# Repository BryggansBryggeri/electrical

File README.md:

# electrical
Electronics, hardware schematics

## Ethernet Cable Wiring Guide
| Colour     	| Connector 	| Temp [DS18B20] 	| VFD  	| Pressure 	| Float switch 	| Albus 	|
|----------	|-------	|----------------	|------	|-------	|-------------	|-------	|
| Orange   	| 1     	| +              	| N/A  	| N/A   	| +           	| N/A   	|
| Blå      	| 2     	| -              	| N/A  	| N/A   	| -           	| N/A   	|
| Brun     	| 3     	| Data           	| N/A  	| N/A   	| N/A         	| N/A   	|
| Grön     	| 4     	| N/A            	| Dif+ 	| N/A   	| N/A         	| N/A   	|
| Grön/Vit 	| 5     	| N/A            	| Dif- 	| N/A   	| N/A         	| N/A   	|

## Panel mounted Contact Orientation

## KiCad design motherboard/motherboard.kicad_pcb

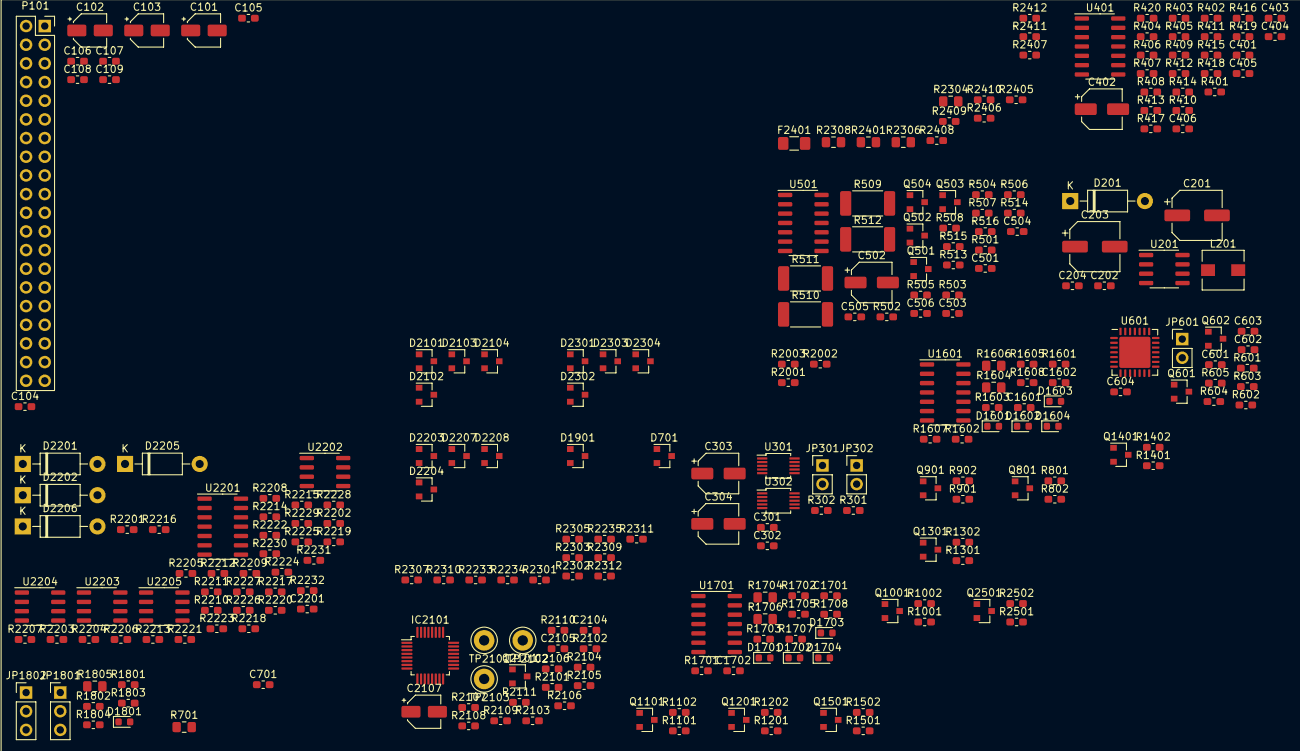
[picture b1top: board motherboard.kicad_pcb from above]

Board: 2 copper layers, 265 parts (0 on the bottom side), 179 nets, no tracks yet.

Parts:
C101, C102, C103, C2107: 1u; CP_Elec_4x5.4
C104, C105, C106, C202: 10n; C_0603_1608Metric_Pad1.05x0.95mm_HandSolder
C107, C108, C109: 100p; C_0603_1608Metric_Pad1.05x0.95mm_HandSolder
C201: 100u; CP_Elec_6.3x5.4_Nichicon
C203: 68u; CP_Elec_6.3x5.8
C204, C2106, C2201: 100n; C_0603_1608Metric_Pad1.05x0.95mm_HandSolder
C301, C302, C2105: 0.1u; C_0603_1608Metric_Pad1.05x0.95mm_HandSolder
C303, C304, C402, C502: 10u; CP_Elec_5x5.4
C401, C403, C404, C405, C406, C501, C503, C504, C505, C506: 2u2; C_0603_1608Metric_Pad1.05x0.95mm_HandSolder
C601, C602: 100pF; C_0603_1608Metric_Pad1.05x0.95mm_HandSolder
C603, C1601, C1701: 100nF; C_0603_1608Metric_Pad1.05x0.95mm_HandSolder
C604, C1602, C1702: 10pF; C_0603_1608Metric_Pad1.05x0.95mm_HandSolder
C701: 220n; C_0603_1608Metric_Pad1.05x0.95mm_HandSolder
C2104: 330n; C_0603_1608Metric_Pad1.05x0.95mm_HandSolder
D201: 1N5817; D_DO-41_SOD81_P10.16mm_Horizontal
D701, D1901, D2101, D2102, D2103, D2104, D2203, D2204, D2207, D2208, D2301, D2302, D2303, D2304: BAT54S; SOT-23
D1601, D1602, D1603, D1604, D1701, D1702, D1703, D1704, D1801: LED; LED_0603_1608Metric
D2201, D2202, D2205, D2206: 1N457; D_DO-41_SOD81_P10.16mm_Horizontal
F2401: 160mA; Fuse_1206_3216Metric_Pad1.42x1.75mm_HandSolder
IC2101: ADS124S08IPBSR; LQFP-32_5x5mm_P0.5mm
JP301, JP302, JP601: Jumper; PinHeader_1x02_P2.54mm_Vertical
JP1801, JP1802: Jumper_3_Bridged12; PinHeader_1x03_P2.54mm_Vertical
L201: 220n; L_Wuerth_HCI-5040
P101: Raspberry_Pi_+_Conn; PinSocket_2x20_P2.54mm_Vertical
Q501, Q502, Q503, Q504, Q601, Q602, Q801, Q901, Q1001, Q1101, Q1201, Q1301, Q1401, Q1501, Q2101, Q2501: Q_NMOS_GSD; SOT-23
R301, R302, R601, R602, R605, R2301, R2303, R2305, R2307: 10k; R_0603_1608Metric_Pad1.05x0.95mm_HandSolder
R401, R402, R403, R404, R501, R502, R503, R504: 22k; R_0603_1608Metric_Pad1.05x0.95mm_HandSolder
R405, R406, R407, R408, R505, R506, R507, R508: 1M; R_0603_1608Metric_Pad1.05x0.95mm_HandSolder
R409, R410, R411, R412: 3k9; R_0603_1608Metric_Pad1.05x0.95mm_HandSolder
R413, R414, R415, R416: 6k8; R_0603_1608Metric_Pad1.05x0.95mm_HandSolder
R417, R418, R419, R420: 1k2; R_0603_1608Metric_Pad1.05x0.95mm_HandSolder
R509, R510, R511, R512: 180R; R_2512_6332Metric_Pad1.52x3.35mm_HandSolder
R513, R514, R515, R516, R801, R901, R1001, R1101, R1201, R1301, R1401, R1501, R1801, R1802, R2107, R2211, R2212, R2227, R2228, R2501: 100k; R_0603_1608Metric_Pad1.05x0.95mm_HandSolder
R603, R604, R2110, R2213, R2214, R2215, R2216, R2229, R2230, R2231, R2232, R2309, R2310, R2311, R2312, R2405, R2406, R2407, R2408, R2409, R2410, R2411, R2412: 1k; R_0603_1608Metric_Pad1.05x0.95mm_HandSolder
R701, R1604, R1606, R1704, R1706, R1805: 220; R_0805_2012Metric_Pad1.15x1.40mm_HandSolder
R802, R902, R1002, R1102, R1202, R1302, R1402, R1502, R2502: 5.6; R_0603_1608Metric_Pad1.05x0.95mm_HandSolder
R1601, R1603, R1605, R1607, R1701, R1703, R1705, R1707: 4k7; R_0603_1608Metric_Pad1.05x0.95mm_HandSolder
R1602, R1608, R1702, R1708: 220; R_0603_1608Metric_Pad1.05x0.95mm_HandSolder
R1803: 3k3; R_0603_1608Metric_Pad1.05x0.95mm_HandSolder
R1804: 5k6; R_0603_1608Metric_Pad1.05x0.95mm_HandSolder
R2001, R2002: 100; R_0603_1608Metric_Pad1.05x0.95mm_HandSolder
R2003: 4.7k; R_0603_1608Metric_Pad1.05x0.95mm_HandSolder
R2101, R2103: R; R_0603_1608Metric_Pad1.05x0.95mm_HandSolder
R2102, R2104, R2105, R2106, R2108, R2109, R2111: 47R; R_0603_1608Metric_Pad1.05x0.95mm_HandSolder
R2201, R2202, R2217, R2218: 75R; R_0603_1608Metric_Pad1.05x0.95mm_HandSolder
R2203, R2204, R2219, R2220: 750R; R_0603_1608Metric_Pad1.05x0.95mm_HandSolder
R2205, R2207, R2208, R2210, R2221, R2223, R2224, R2226: 20k; R_0603_1608Metric_Pad1.05x0.95mm_HandSolder
R2206, R2209, R2222, R2225: 28k; R_0603_1608Metric_Pad1.05x0.95mm_HandSolder
R2233, R2234, R2235, R2302: 2k7; R_0603_1608Metric_Pad1.05x0.95mm_HandSolder
R2304, R2306, R2308, R2401: 120R; R_0805_2012Metric_Pad1.15x1.40mm_HandSolder
TP2101, TP2102, TP2103: TestPoint; TestPoint_Loop_D3.50mm_Drill1.4mm_Beaded
U201: LM2674M-12; SOIC-8_3.9x4.9mm_P1.27mm
U301, U302: MCP4728; MSOP-10_3x3mm_P0.5mm
U401, U501, U1601, U1701, U2201: LM324; SOIC-14_3.9x8.7mm_P1.27mm
U601: MCP23017_ML; QFN-28-1EP_6x6mm_P0.65mm_EP4.25x4.25mm
U2202, U2203, U2204, U2205: LM334M; SOIC-8_3.9x4.9mm_P1.27mm

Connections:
+3V3: C102.1, C105.1, C108.1, C2105.1, D1901.2, IC2101.15, IC2101.16, P101.1, Q601.1, Q602.1, Q2101.3, R601.2, R602.2, R2003.1
+5V: C101.1, C104.1, C107.1, C603.1, C604.1, C1601.1, C1602.1, C1701.1, C1702.1, C2104.1, C2106.1, C2201.1, IC2101.26, JP301.2, JP302.2, JP601.1, P101.2, P101.4, R603.1, R604.1, R701.1, U601.5, U1601.4, U1701.4, U2201.4
+12V: C203.1, C204.1, L201.2, U201.4, U401.4, U501.4
+24V: C103.1, C106.1, C109.1, C201.1, F2401.2, U201.5, U201.7
/ADC_START_SYNC: P101.36, R2102.2
/Analog inputs/10V_A: IC2101.3, R2309.1
/Analog inputs/10V_B: IC2101.2, R2310.1
/Analog inputs/10V_C: IC2101.32, R2311.1
/Analog inputs/10V_D: IC2101.31, R2312.1
/Analog inputs/20mA-1-4/A_in_low: R2401.1, R2405.2
/Analog inputs/20mA-1-4/B_in_low: R2304.1, R2406.2
/Analog inputs/20mA-1-4/C_in_low: R2306.1, R2407.2
/Analog inputs/20mA-1-4/D_in_low: R2308.1, R2408.2
/Analog inputs/20mA-1-4/Vref: D2301.2, D2302.2, D2303.2, D2304.2
/Analog inputs/20mA_A: IC2101.22, R2409.1
/Analog inputs/20mA_B: IC2101.21, R2410.1
/Analog inputs/20mA_C: IC2101.20, R2411.1
/Analog inputs/20mA_D: IC2101.19, R2412.1
/Analog inputs/PT100_A: IC2101.7, R2215.1
/Analog inputs/PT100_B: IC2101.6, R2231.1
/Analog inputs/PT100_C: IC2101.5, R2216.1
/Analog inputs/PT100_D: IC2101.4, R2232.1
/Analog inputs/PT-100-1/A_pos: D2201.1, R2203.1, R2206.2
/Analog inputs/Vref: C2107.1, IC2101.23, R2101.2
/Analog inputs/Vref_buf: D2101.2, D2102.2, D2103.2, D2104.2, D2203.2, D2204.2, D2207.2, D2208.2, Q2101.2, R2110.1, TP2103.1, U2202.4, U2203.4, U2204.4, U2205.4
/DAC/A_out_10V: R413.1, R417.2
/DAC/B_out_10V: R414.1, R418.2
/DAC/C_out_10V: R415.1, R419.2
/DAC/DAC current loop amp/A_in: R504.2, U302.6
/DAC/DAC current loop amp/B_in: R501.2, U302.7
/DAC/DAC current loop amp/C_in: R502.2, U302.8
/DAC/DAC current loop amp/D_in: R503.2, U302.9
/DAC/DAC_amp/A_in: R401.2, U301.6
/DAC/DAC_amp/B_in: R402.2, U301.7
/DAC/DAC_amp/C_in: R403.2, U301.8
/DAC/DAC_amp/D_in: R404.2, U301.9
/DAC/D_out_10V: R416.1, R420.2
/DAC/sda: P101.3, Q601.2, R601.1, U301.3, U302.3
/SPI_MISO: P101.21, R2108.2
/SPI_MOSI: P101.19, R2105.2
/SPI_SCLK: P101.23, R2106.2
/SSR_1_ind: R1601.2, U601.25
/SSR_2_ind: R1603.2, U601.26
/SSR_interface/SSR1_GPIO: JP1801.3, R1802.1, U601.17
/SSR_interface/SSR1_GPIO_safe: JP1801.2, Q1001.1, R1001.1
/SSR_interface/SSR2_GPIO: JP1802.3, R1801.1, U601.18
/SSR_interface/SSR2_GPIO_safe: JP1802.2, Q801.1, R801.1
/SSR_interface/error_signal: P101.18, R1803.1, R1804.1
/Safety stop/indicator: Q2501.2, R2502.1
/Safety stop/sig_in: P101.16, Q2501.1, R2501.1
/extra_1_ind: R1607.2, U601.27
/extra_2_ind: R1605.2, U601.28
/i2c_interface/relay_1_i2c_out: Q1501.1, R1501.1, U601.21
/i2c_interface/relay_2_i2c_out: Q1401.1, R1401.1, U601.22
/i2c_interface/relay_3_i2c_out: Q1301.1, R1301.1, U601.23
/i2c_interface/relay_4_i2c_out: Q901.1, R901.1, U601.24
/i2c_interface/sck: P101.5, Q602.2, R602.1, U301.2, U302.2
/low_side_outputs/SSR1_driver/indicator: Q1001.2, R1002.1, U1601.3
/low_side_outputs/SSR2_driver/indicator: Q801.2, R802.1, U1601.5
/low_side_outputs/SSR_1_2_comparator/reference_voltage: C701.1, U1601.2, U1601.6, U1601.9, U1601.13, U1701.2, U1701.6, U1701.9, U1701.13
/low_side_outputs/extra_1_driver/indicator: Q1101.2, R1102.1, U1601.10
/low_side_outputs/extra_1_in: Q1101.1, R1101.1, U601.19
/low_side_outputs/extra_2_driver/indicator: Q1201.2, R1202.1, U1601.12
/low_side_outputs/extra_2_in: Q1201.1, R1201.1, U601.20
/low_side_outputs/relay_1_driver/indicator: Q1501.2, R1502.1, U1701.3
/low_side_outputs/relay_2_driver/indicator: Q1401.2, R1402.1, U1701.5
/low_side_outputs/relay_3_driver/indicator: Q1301.2, R1302.1, U1701.10
/low_side_outputs/relay_4_driver/indicator: Q901.2, R902.1, U1701.12
/relay_1_ind: R1701.2, U601.1
/relay_2_ind: R1703.2, U601.2
/relay_3_ind: R1707.2, U601.3
/relay_4_ind: R1705.2, U601.4
/temp_interface/TEMP_GPIO: P101.7, R2001.2
/temp_interface/TEMP_IN: R2002.1, R2003.2
/~ADC_CS: P101.24, R2104.2
/~ADC_DRDY: P101.32, R2109.2
/~ADC_RESET: P101.33, R2111.2
GND: C101.2, C102.2, C103.2, C104.2, C105.2, C106.2, C107.2, C108.2, C109.2, C201.2, C203.2, C204.2, C301.2, C302.2, C303.2, C304.2, C403.2, C404.2, C405.2, C406.2, C503.2, C504.2, C505.2, C506.2, C601.2, C602.2, C603.2, C604.2, C701.2, C1601.2, C1602.2, C1701.2, C1702.2, C2104.2, C2105.2, C2106.2, C2107.2, C2201.2, D201.2, D701.2, D1601.1, D1602.1, D1603.1, D1604.1, D1701.1, D1702.1, D1703.1, D1704.1, D1801.1, D1901.1, D2203.1, D2204.1, D2207.1, D2208.1, D2301.1, D2302.1, D2303.1, D2304.1, IC2101.1, IC2101.14, IC2101.17, IC2101.24, IC2101.27, IC2101.28, P101.6, P101.9, P101.14, P101.20, P101.25, P101.30, P101.34, P101.39, R301.2, R302.2, R405.1, R406.1, R407.1, R408.1, R409.2, R410.2, R411.2, R412.2, R505.1, R506.1, R507.1, R508.1, R509.2, R510.2, R511.2, R512.2, R513.2, R514.2, R515.2, R516.2, R605.2, R801.2, R802.2, R901.2, R902.2, R1001.2, R1002.2, R1101.2, R1102.2, R1201.2, R1202.2, R1301.2, R1302.2, R1401.2, R1402.2, R1501.2, R1502.2, R1801.2, R1802.2, R1804.2, R2107.2, R2110.2, R2205.2, R2208.2, R2221.2, R2224.2, R2233.2, R2234.2, R2235.2, R2302.2, R2304.2, R2306.2, R2308.2, R2401.2, R2501.2, R2502.2, U201.6, U301.10, U302.10, U401.11, U501.11, U601.6, U601.11, U601.12, U601.13, U601.29, U1601.11, U1701.11, U2201.11
unnamed: C202.1, D201.1, L201.1, U201.8
unnamed: C202.2, U201.1
unnamed: C301.1, C303.1, JP301.1, U301.1
unnamed: C302.1, C304.1, JP302.1, U302.1
unnamed: C401.1, C402.1
unnamed: C401.2, C402.2
unnamed: C403.1, R401.1, R405.2, U401.3
unnamed: C404.1, R402.1, R406.2, U401.5
unnamed: C405.1, R403.1, R407.2, U401.10
unnamed: C406.1, R404.1, R408.2, U401.12
unnamed: C501.1, C502.1
unnamed: C501.2, C502.2
unnamed: C503.1, R501.1, R505.2, U501.5
unnamed: C504.1, R502.1, R506.2, U501.10
unnamed: C505.1, R503.1, R507.2, U501.12
unnamed: C506.1, R504.1, R508.2, U501.3
unnamed: C601.1, Q601.3, R603.2, U601.9
unnamed: C602.1, Q602.3, R604.2, U601.8
unnamed: R2101.1, TP2101.1
unnamed: Q2101.1, R2103.1, R2107.1, TP2102.1
unnamed: D701.1, R701.2
unnamed: D1601.2, R1602.2
unnamed: D1602.2, R1604.2
unnamed: D1603.2, R1606.2
unnamed: D1604.2, R1608.2
unnamed: D1701.2, R1702.2
unnamed: D1702.2, R1704.2
unnamed: D1703.2, R1706.2
unnamed: D1704.2, R1708.2
unnamed: D1801.2, R1805.2
unnamed: D1901.3, R2001.1, R2002.2
unnamed: D2101.3, R2213.1, R2215.2
unnamed: D2102.3, R2214.1, R2216.2
unnamed: D2103.3, R2229.1, R2231.2
unnamed: D2104.3, R2230.1, R2232.2
unnamed: D2202.1, R2204.1
unnamed: D2203.3, R2301.2, R2302.1, R2309.2
unnamed: D2204.3, R2233.1, R2303.2, R2310.2
unnamed: D2205.1, R2219.1
unnamed: D2206.1, R2220.1
unnamed: D2207.3, R2234.1, R2305.2, R2311.2
unnamed: D2208.3, R2235.1, R2307.2, R2312.2
unnamed: D2301.3, R2405.1, R2409.2
unnamed: D2302.3, R2406.1, R2410.2
unnamed: D2303.3, R2407.1, R2411.2
unnamed: D2304.3, R2408.1, R2412.2
unnamed: IC2101.8, R2102.1
unnamed: IC2101.9, R2104.1
unnamed: IC2101.10, R2105.1
unnamed: IC2101.11, R2106.1
unnamed: IC2101.12, R2108.1
unnamed: IC2101.13, R2109.1
unnamed: IC2101.18, R2111.1
unnamed: JP601.2, R605.1, U601.14
unnamed: Q501.1, R513.1, U501.7
unnamed: Q501.2, R509.1, U501.6
unnamed: Q502.1, R514.1, U501.8
unnamed: Q502.2, R510.1, U501.9
unnamed: Q503.1, R515.1, U501.14
unnamed: Q503.2, R511.1, U501.13
unnamed: Q504.1, R516.1, U501.1
unnamed: Q504.2, R512.1, U501.2
unnamed: R301.1, U301.4
unnamed: R302.1, U302.4
unnamed: R409.1, R413.2, U401.2
unnamed: R410.1, R414.2, U401.6
unnamed: R411.1, R415.2, U401.9
unnamed: R412.1, R416.2, U401.13
unnamed: R417.1, U401.1
unnamed: R418.1, U401.7
unnamed: R419.1, U401.8
unnamed: R420.1, U401.14
unnamed: R1601.1, R1602.1, U1601.1
unnamed: R1603.1, R1604.1, U1601.7
unnamed: R1605.1, R1606.1, U1601.8
unnamed: R1607.1, R1608.1, U1601.14
unnamed: R1701.1, R1702.1, U1701.1
unnamed: R1703.1, R1704.1, U1701.7
unnamed: R1705.1, R1706.1, U1701.8
unnamed: R1707.1, R1708.1, U1701.14
unnamed: R1803.2, R1805.1
unnamed: R2201.2, R2203.2, U2202.1
unnamed: R2202.2, R2204.2, U2203.1
unnamed: R2205.1, R2206.1, U2201.3
unnamed: R2207.1, R2211.2, U2201.2
unnamed: R2208.1, R2209.1, U2201.10
unnamed: R2210.1, R2212.2, U2201.9
unnamed: R2211.1, R2213.2, U2201.1
unnamed: R2212.1, R2214.2, U2201.8
unnamed: R2217.2, R2219.2, U2204.1
unnamed: R2218.2, R2220.2, U2205.1
unnamed: R2221.1, R2222.1, U2201.5
unnamed: R2223.1, R2227.2, U2201.6
unnamed: R2224.1, R2225.1, U2201.12
unnamed: R2226.1, R2228.2, U2201.13
unnamed: R2227.1, R2229.2, U2201.7
unnamed: R2228.1, R2230.2, U2201.14
unnamed: U2202.2, U2202.3, U2202.6, U2202.7
unnamed: U2203.2, U2203.3, U2203.6, U2203.7
unnamed: U2204.2, U2204.3, U2204.6, U2204.7
unnamed: U2205.2, U2205.3, U2205.6, U2205.7

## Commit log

2018-11-21 Initial commit of electrical schema
    Starting to design the circuits in the brew enclosure
    Building from the rbpi and outwards.
    Added separate functions as hierarchical sheets,
    not sure if this is best practice.
2018-11-21 Ported Gjellegras to new project structure
2018-11-21 Better automatic naming
2018-11-21 Float switch to AND gate
2018-11-22 N-MOSFET driven SSR
    Also opamp comparator for led indication that the SSR's are driven
    Only one SSR is connected since it's a WIP
2018-12-07 First Motherboard verison ready!
    Changes done at ETA 18-12-06:
    - Moved ssr driver to separate sheet
    - Added gpio protection for temperature sensor
    - Assigned correct footprints
    - Calculated resistor values
2018-12-07 +5V: Component --> Power flag
    Had made a custom power component for the voltage. That was a mistake
    Fixed now: as in no footprints needed for all the power flags
2018-12-10 WIP xor
2018-12-12 Alternate XOR implementation
    Instead of actual XOR + AND we use NOT + AND
    Now done with only two components:
    one dual AND and one quad 2-input AND (only triple in use)
2018-12-12 Spread all footprints out
2018-12-13 First routing done!
2018-12-13 Moved parts around
2019-01-02 Ready for print?
2019-01-08 Changing hard library references to relative
2019-01-08 Added second SSR connector
2019-01-08 Moving to RPI hat PCB
2019-02-01 Thinkpad transfer
2019-03-12 Library fix
2019-03-20 Cosmetic changes
2019-03-20 Fixed dual and
2019-03-20 Logo
2019-03-20 Rev1.0 as sent to print
2019-03-21 gitiggggg
2019-03-21 Started enclosure schematic
2019-03-21 File structure
2019-03-21 Added motherboard
    Motherboard (rbpi) as a hierarchical sheet
    Needed to do some changes in order to expose hier. pins to enclosure.
2019-03-21 Enclosure schematic start
2019-03-22 Enclosure Rev 0.5
    Key + Emergency stop breaks N not L1 (i.e. after contactor)
2019-03-22 Relative lib paths
2019-03-22 Splits, SSR driver bug
2019-03-22 Added: SSR fan, Proper splits
2019-03-22 Split measurement block
2019-03-23 Proper N for DZ lamp. Nicer symbols
2019-03-26 Full wiring
2019-05-03 Phase -> GND bug
2019-05-03 Larger fontsize
2019-05-06 WIP: Changing offices
2019-05-14 Correct power splits, rewire
2019-05-15 10A fuses + ssr signal bug fix
2019-05-15 More advanced 3P relay
2019-05-15 Tmp prototype relay
2019-05-16 New file: Drawing from Power in -> Splitter
2019-05-16 My take on the new double relay design
    - Relay symbol from lib
    - Emergency and key in series
2019-05-16 Added proper split for relay14
2019-06-28 For Jontes eyes only
2019-07-01 Relay security as sent to Loka
2019-07-01 Restructure no cable
2019-07-01 Library changes for simpler wiring
2019-07-01 Low hanging wires
2019-07-01 Everything but double contactor and sensor
2019-07-01 v0.6 Feature complete!!!
2019-07-02 220V relay corrct pins
2019-07-04 Annotations and patch version
2019-07-22 coloured pdf added. Revision 0.8
2019-07-22 Added pdf for full enclosure drawing revision 0.8
2019-08-12 Updated schematic to show actual wiring impl
2019-08-12 Control lamp with dummy relay
2019-08-13 Control lamp behaviour fix
    Removed dummy relay and split phase after emergency+key
    with additional line going to NC-aux on relay pair,
    up to control lamp.
    This will make the control lamp ON if the following conditions are ALL
    true:
    - emergency not active
2019-08-13 Bug in schema 220V relay
    Change relay A1/A2 wiring s.t. the transistor break is after the relay
    (opens to ground)
2019-08-15 Added connector and hier. pins for temp
2019-08-16 WIP: Motherboard v1.1
    - Moved all connectors to root hierarchical sheet => More modular
    - Removed GND connectors for the 24VDC signals (not needed)
    - Changed 24VDC connectors to a single 1x8 phoenix connector
    - Removed connectors for SSR indicator and error signal. Indicators are
    redundant (230V lamp directly on SSR out phase instead). Error
    potentially useful. Instead these signals should be feedbacked to
2019-08-16 Grounded all ground pins on rbpi
2019-08-16 Hier root
    - Added serial comm template hier. sheet
    - Feedback ssr signals. NB: the signal needs to be adapted for gpio in
    the actual hier. sheet
2019-08-16 Serial connectors
2019-08-16 Renaming quantities
2019-08-16 Beginning work with Forss
2019-08-16 WIP: low side driver split
2019-08-16 WIP: Motherboard v1.1
    - UART for VFD only
    - i2c for io expansion
    - All 24VDC with common drivers
2019-08-19 WIP: Motherboard v1.1
    Cosmetic changes
2019-08-19 Float switch
    Included simplest wiring proposal where no indication is present.
    The float switch literally switches the the 24VDC signal to the SSR
2019-08-19 Exported new rev1.1 to all subsheets
2019-08-19 Float switch proposal
    Needs review!!!
    driver signal (24VDC) is interrupted by transistor with float switch
    connected to G. Multiple transistors in parallell allows for any signal
    to be independently triggered by float switch, i.e. SSR, indicator, rbpi
    feedback
2019-08-23 Temp sens wire enclosure
2019-08-23 Prototype i2c sub-schema
2019-08-23 Fixed relay bug A1 wired to L3 NOT 24VDC, now fixed
2019-08-29 Enclosure closed switch in kicad
2019-08-29 i2c interface
2019-08-29 To quad op amp
2019-08-29 No bugs in eeschema
    Netlists
    Footprints
    All is well
2019-08-30 Fixed edge cuts bug
2019-08-30 i2c subcircuit routed
2019-08-30 Showcase PCB
2019-10-21 Creat Readme + Etherner Cable Wiring Guide
    Documentation of Ethernet wiring
2019-10-21 Add image of
2019-10-21 Update Readme with image
2020-02-27 Tried some placements
2020-03-19 Major design work
    - General DAC interface
    - 5V --> 12V boost
2020-03-20 Swap to buck from 24V and add 4-20mA control
2020-03-20 Prepare for analog measurments
2020-03-21 Add 0-10V and 4-20mA inputs
2020-03-21 Add ADC Vref buffer chopping opamp
2020-03-21 Swap in and out in IO-expander
    This is so the "read" register is lower then "write".
2020-03-21 Set SSRX_GPIO_safe to output
2020-03-21 Swap order if IO-expander to match PHY
2020-03-21 Straighten some wires
2020-03-21 Reconnect lables from move
2020-03-21 Make SSR mutex bypassable
2020-03-21 Swap open drain inouts to match registers
2020-03-21 Fix some bypassing
2020-03-22 Add PT100 measurements
2020-03-23 Relative lib path
2020-03-23 Simplify PT-100 biasing
2020-03-23 Add ADC
2020-03-23 Fix DRC errors
2020-03-23 Move IO-expander address select to outside
    This is to enable us to easier have more expanders in the future
2020-03-23 Move some lables for better readability
2020-03-24 Start moving 4-20mA biasing to reciever
2020-03-24 Add more on the revised version of 4-20mA controll
2020-04-03 Amazing work
2020-05-28 Do footprint assissiation
2020-06-30 Double diodes, removed v_ref buffer.
    fixes #83
